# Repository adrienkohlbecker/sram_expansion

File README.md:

# SRAM expansion

## Board

## Schematic

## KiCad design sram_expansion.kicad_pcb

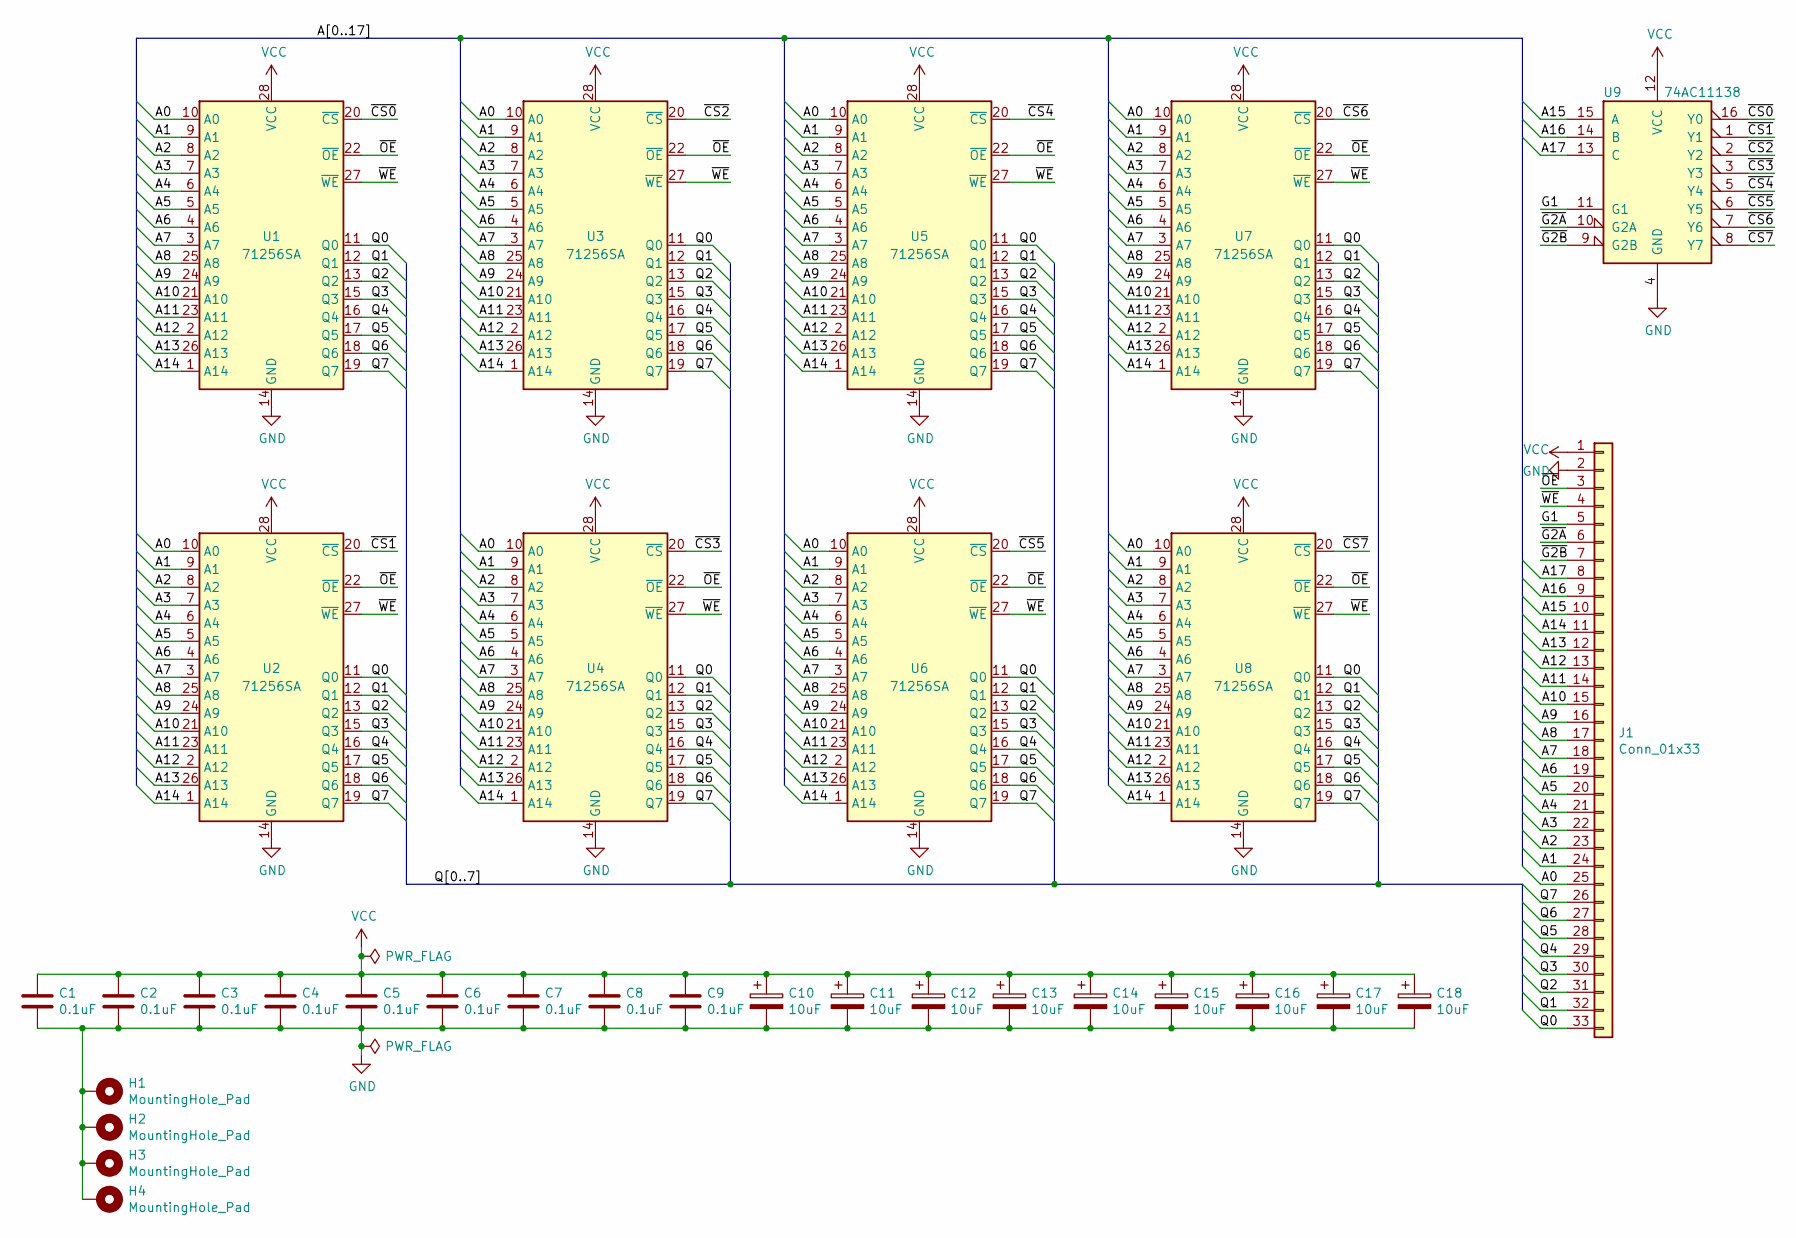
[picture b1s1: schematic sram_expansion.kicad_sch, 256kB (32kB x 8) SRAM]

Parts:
C1, C2, C3, C4, C5, C6, C7, C8, C9: 0.1uF; C_0805_2012Metric_Pad1.18x1.45mm_HandSolder
C10, C11, C12, C13, C14, C15, C16, C17, C18: 10uF; C_0805_2012Metric_Pad1.18x1.45mm_HandSolder
H1, H2, H3, H4: MountingHole_Pad; MountingHole_3.2mm_M3_Pad
J1: Conn_01x33; PinSocket_1x33_P2.54mm_Vertical
U1, U2, U3, U4, U5, U6, U7, U8: 71256SA; DIP-28_W7.62mm
U9: 74AC11138; DIP-16_W7.62mm

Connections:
/A0: J1.25, U1.10 (A0), U2.10 (A0), U3.10 (A0), U4.10 (A0), U5.10 (A0), U6.10 (A0), U7.10 (A0), U8.10 (A0)
/A1: J1.24, U1.9 (A1), U2.9 (A1), U3.9 (A1), U4.9 (A1), U5.9 (A1), U6.9 (A1), U7.9 (A1), U8.9 (A1)
/A2: J1.23, U1.8 (A2), U2.8 (A2), U3.8 (A2), U4.8 (A2), U5.8 (A2), U6.8 (A2), U7.8 (A2), U8.8 (A2)
/A3: J1.22, U1.7 (A3), U2.7 (A3), U3.7 (A3), U4.7 (A3), U5.7 (A3), U6.7 (A3), U7.7 (A3), U8.7 (A3)
/A4: J1.21, U1.6 (A4), U2.6 (A4), U3.6 (A4), U4.6 (A4), U5.6 (A4), U6.6 (A4), U7.6 (A4), U8.6 (A4)
/A5: J1.20, U1.5 (A5), U2.5 (A5), U3.5 (A5), U4.5 (A5), U5.5 (A5), U6.5 (A5), U7.5 (A5), U8.5 (A5)
/A6: J1.19, U1.4 (A6), U2.4 (A6), U3.4 (A6), U4.4 (A6), U5.4 (A6), U6.4 (A6), U7.4 (A6), U8.4 (A6)
/A7: J1.18, U1.3 (A7), U2.3 (A7), U3.3 (A7), U4.3 (A7), U5.3 (A7), U6.3 (A7), U7.3 (A7), U8.3 (A7)
/A8: J1.17, U1.25 (A8), U2.25 (A8), U3.25 (A8), U4.25 (A8), U5.25 (A8), U6.25 (A8), U7.25 (A8), U8.25 (A8)
/A9: J1.16, U1.24 (A9), U2.24 (A9), U3.24 (A9), U4.24 (A9), U5.24 (A9), U6.24 (A9), U7.24 (A9), U8.24 (A9)
/A10: J1.15, U1.21 (A10), U2.21 (A10), U3.21 (A10), U4.21 (A10), U5.21 (A10), U6.21 (A10), U7.21 (A10), U8.21 (A10)
/A11: J1.14, U1.23 (A11), U2.23 (A11), U3.23 (A11), U4.23 (A11), U5.23 (A11), U6.23 (A11), U7.23 (A11), U8.23 (A11)
/A12: J1.13, U1.2 (A12), U2.2 (A12), U3.2 (A12), U4.2 (A12), U5.2 (A12), U6.2 (A12), U7.2 (A12), U8.2 (A12)
/A13: J1.12, U1.26 (A13), U2.26 (A13), U3.26 (A13), U4.26 (A13), U5.26 (A13), U6.26 (A13), U7.26 (A13), U8.26 (A13)
/A14: J1.11, U1.1 (A14), U2.1 (A14), U3.1 (A14), U4.1 (A14), U5.1 (A14), U6.1 (A14), U7.1 (A14), U8.1 (A14)
/A15: J1.10, U9.15 (A)
/A16: J1.9, U9.14 (B)
/A17: J1.8, U9.13 (C)
/G1: J1.5, U9.11 (G1)
/Q0: J1.33, U1.11 (Q0), U2.11 (Q0), U3.11 (Q0), U4.11 (Q0), U5.11 (Q0), U6.11 (Q0), U7.11 (Q0), U8.11 (Q0)
/Q1: J1.32, U1.12 (Q1), U2.12 (Q1), U3.12 (Q1), U4.12 (Q1), U5.12 (Q1), U6.12 (Q1), U7.12 (Q1), U8.12 (Q1)
/Q2: J1.31, U1.13 (Q2), U2.13 (Q2), U3.13 (Q2), U4.13 (Q2), U5.13 (Q2), U6.13 (Q2), U7.13 (Q2), U8.13 (Q2)
/Q3: J1.30, U1.15 (Q3), U2.15 (Q3), U3.15 (Q3), U4.15 (Q3), U5.15 (Q3), U6.15 (Q3), U7.15 (Q3), U8.15 (Q3)
/Q4: J1.29, U1.16 (Q4), U2.16 (Q4), U3.16 (Q4), U4.16 (Q4), U5.16 (Q4), U6.16 (Q4), U7.16 (Q4), U8.16 (Q4)
/Q5: J1.28, U1.17 (Q5), U2.17 (Q5), U3.17 (Q5), U4.17 (Q5), U5.17 (Q5), U6.17 (Q5), U7.17 (Q5), U8.17 (Q5)
/Q6: J1.27, U1.18 (Q6), U2.18 (Q6), U3.18 (Q6), U4.18 (Q6), U5.18 (Q6), U6.18 (Q6), U7.18 (Q6), U8.18 (Q6)
/Q7: J1.26, U1.19 (Q7), U2.19 (Q7), U3.19 (Q7), U4.19 (Q7), U5.19 (Q7), U6.19 (Q7), U7.19 (Q7), U8.19 (Q7)
/~CS0: U1.20 (~CS), U9.16 (Y0)
/~CS1: U2.20 (~CS), U9.1 (Y1)
/~CS2: U3.20 (~CS), U9.2 (Y2)
/~CS3: U4.20 (~CS), U9.3 (Y3)
/~CS4: U5.20 (~CS), U9.5 (Y4)
/~CS5: U6.20 (~CS), U9.6 (Y5)
/~CS6: U7.20 (~CS), U9.7 (Y6)
/~CS7: U8.20 (~CS), U9.8 (Y7)
/~G2A: J1.6, U9.10 (G2A)
/~G2B: J1.7, U9.9 (G2B)
/~OE: J1.3, U1.22 (~OE), U2.22 (~OE), U3.22 (~OE), U4.22 (~OE), U5.22 (~OE), U6.22 (~OE), U7.22 (~OE), U8.22 (~OE)
/~WE: J1.4, U1.27 (~WE), U2.27 (~WE), U3.27 (~WE), U4.27 (~WE), U5.27 (~WE), U6.27 (~WE), U7.27 (~WE), U8.27 (~WE)
GND: C1.2, C2.2, C3.2, C4.2, C5.2, C6.2, C7.2, C8.2, C9.2, C10.2, C11.2, C12.2, C13.2, C14.2, C15.2, C16.2, C17.2, C18.2, H1.1, H2.1, H3.1, H4.1, J1.2, U1.14 (GND), U2.14 (GND), U3.14 (GND), U4.14 (GND), U5.14 (GND), U6.14 (GND), U7.14 (GND), U8.14 (GND), U9.4 (GND)
VCC: C1.1, C2.1, C3.1, C4.1, C5.1, C6.1, C7.1, C8.1, C9.1, C10.1, C11.1, C12.1, C13.1, C14.1, C15.1, C16.1, C17.1, C18.1, J1.1, U1.28 (VCC), U2.28 (VCC), U3.28 (VCC), U4.28 (VCC), U5.28 (VCC), U6.28 (VCC), U7.28 (VCC), U8.28 (VCC), U9.12 (VCC)

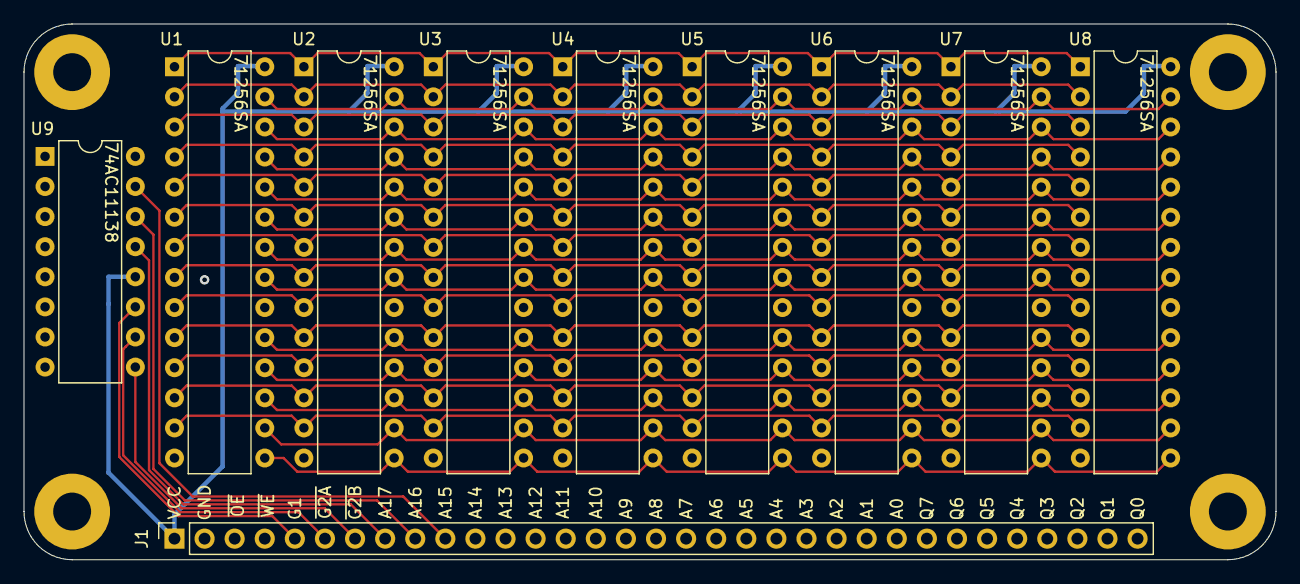
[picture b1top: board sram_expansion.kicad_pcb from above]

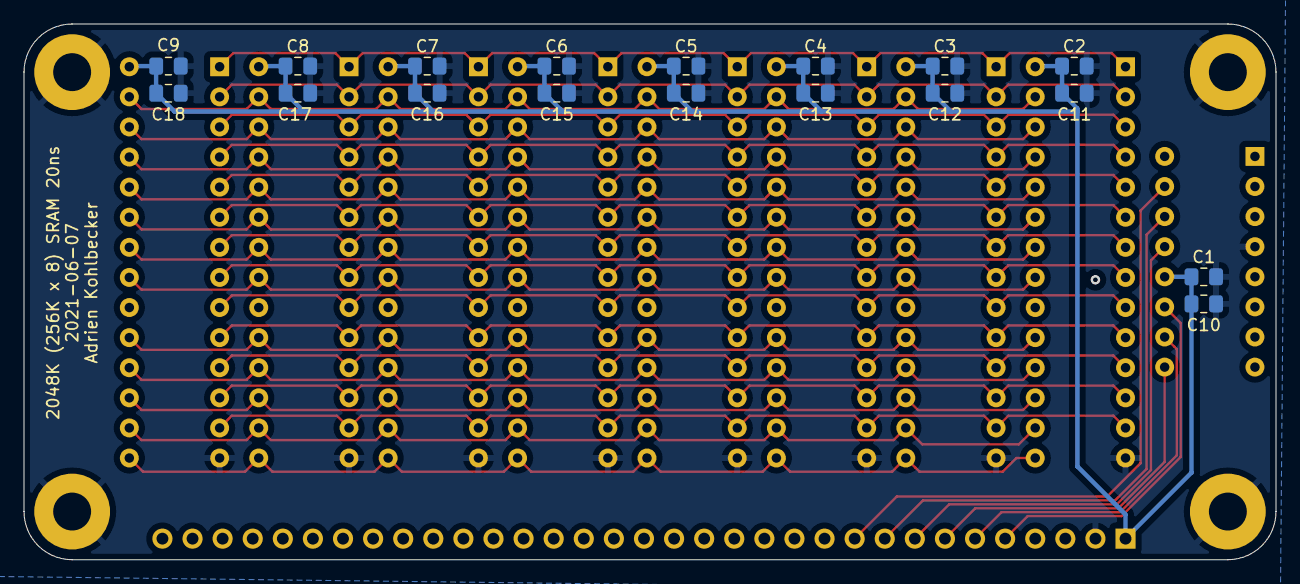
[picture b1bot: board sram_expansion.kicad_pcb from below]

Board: 4 copper layers, 105.7 x 45.2 mm, 32 parts (18 on the bottom side), 41 nets.

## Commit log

2021-07-13 Add video memory
2021-12-19 Remove ignored files
2023-06-07 Update for KiCad 6
